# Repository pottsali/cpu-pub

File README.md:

# MUPS/16 Homebrew CPU project

This is public repo for files from the MUPS/16 homebrew CPU project. Please see http://mups16.net for details.

## Files

### Schematics
Currently I've only uploaded the schematics for the PCBs here, and will add more as I complete the last few bits. Most of the schematics are documented on the MUPS/16 [website](http://mups16.net).

### Others
I have a few other sets of files to clean up and upload:
 - A gate-level simulation of the whole system in [Digital](https://github.com/hneemann/Digital) format
 - Microcode generation, for the control ROMs
 - An assembler
 - A very basic monitor to test the system
 
These are not yet in a fit state to upload, but I will add them as I clean them up.

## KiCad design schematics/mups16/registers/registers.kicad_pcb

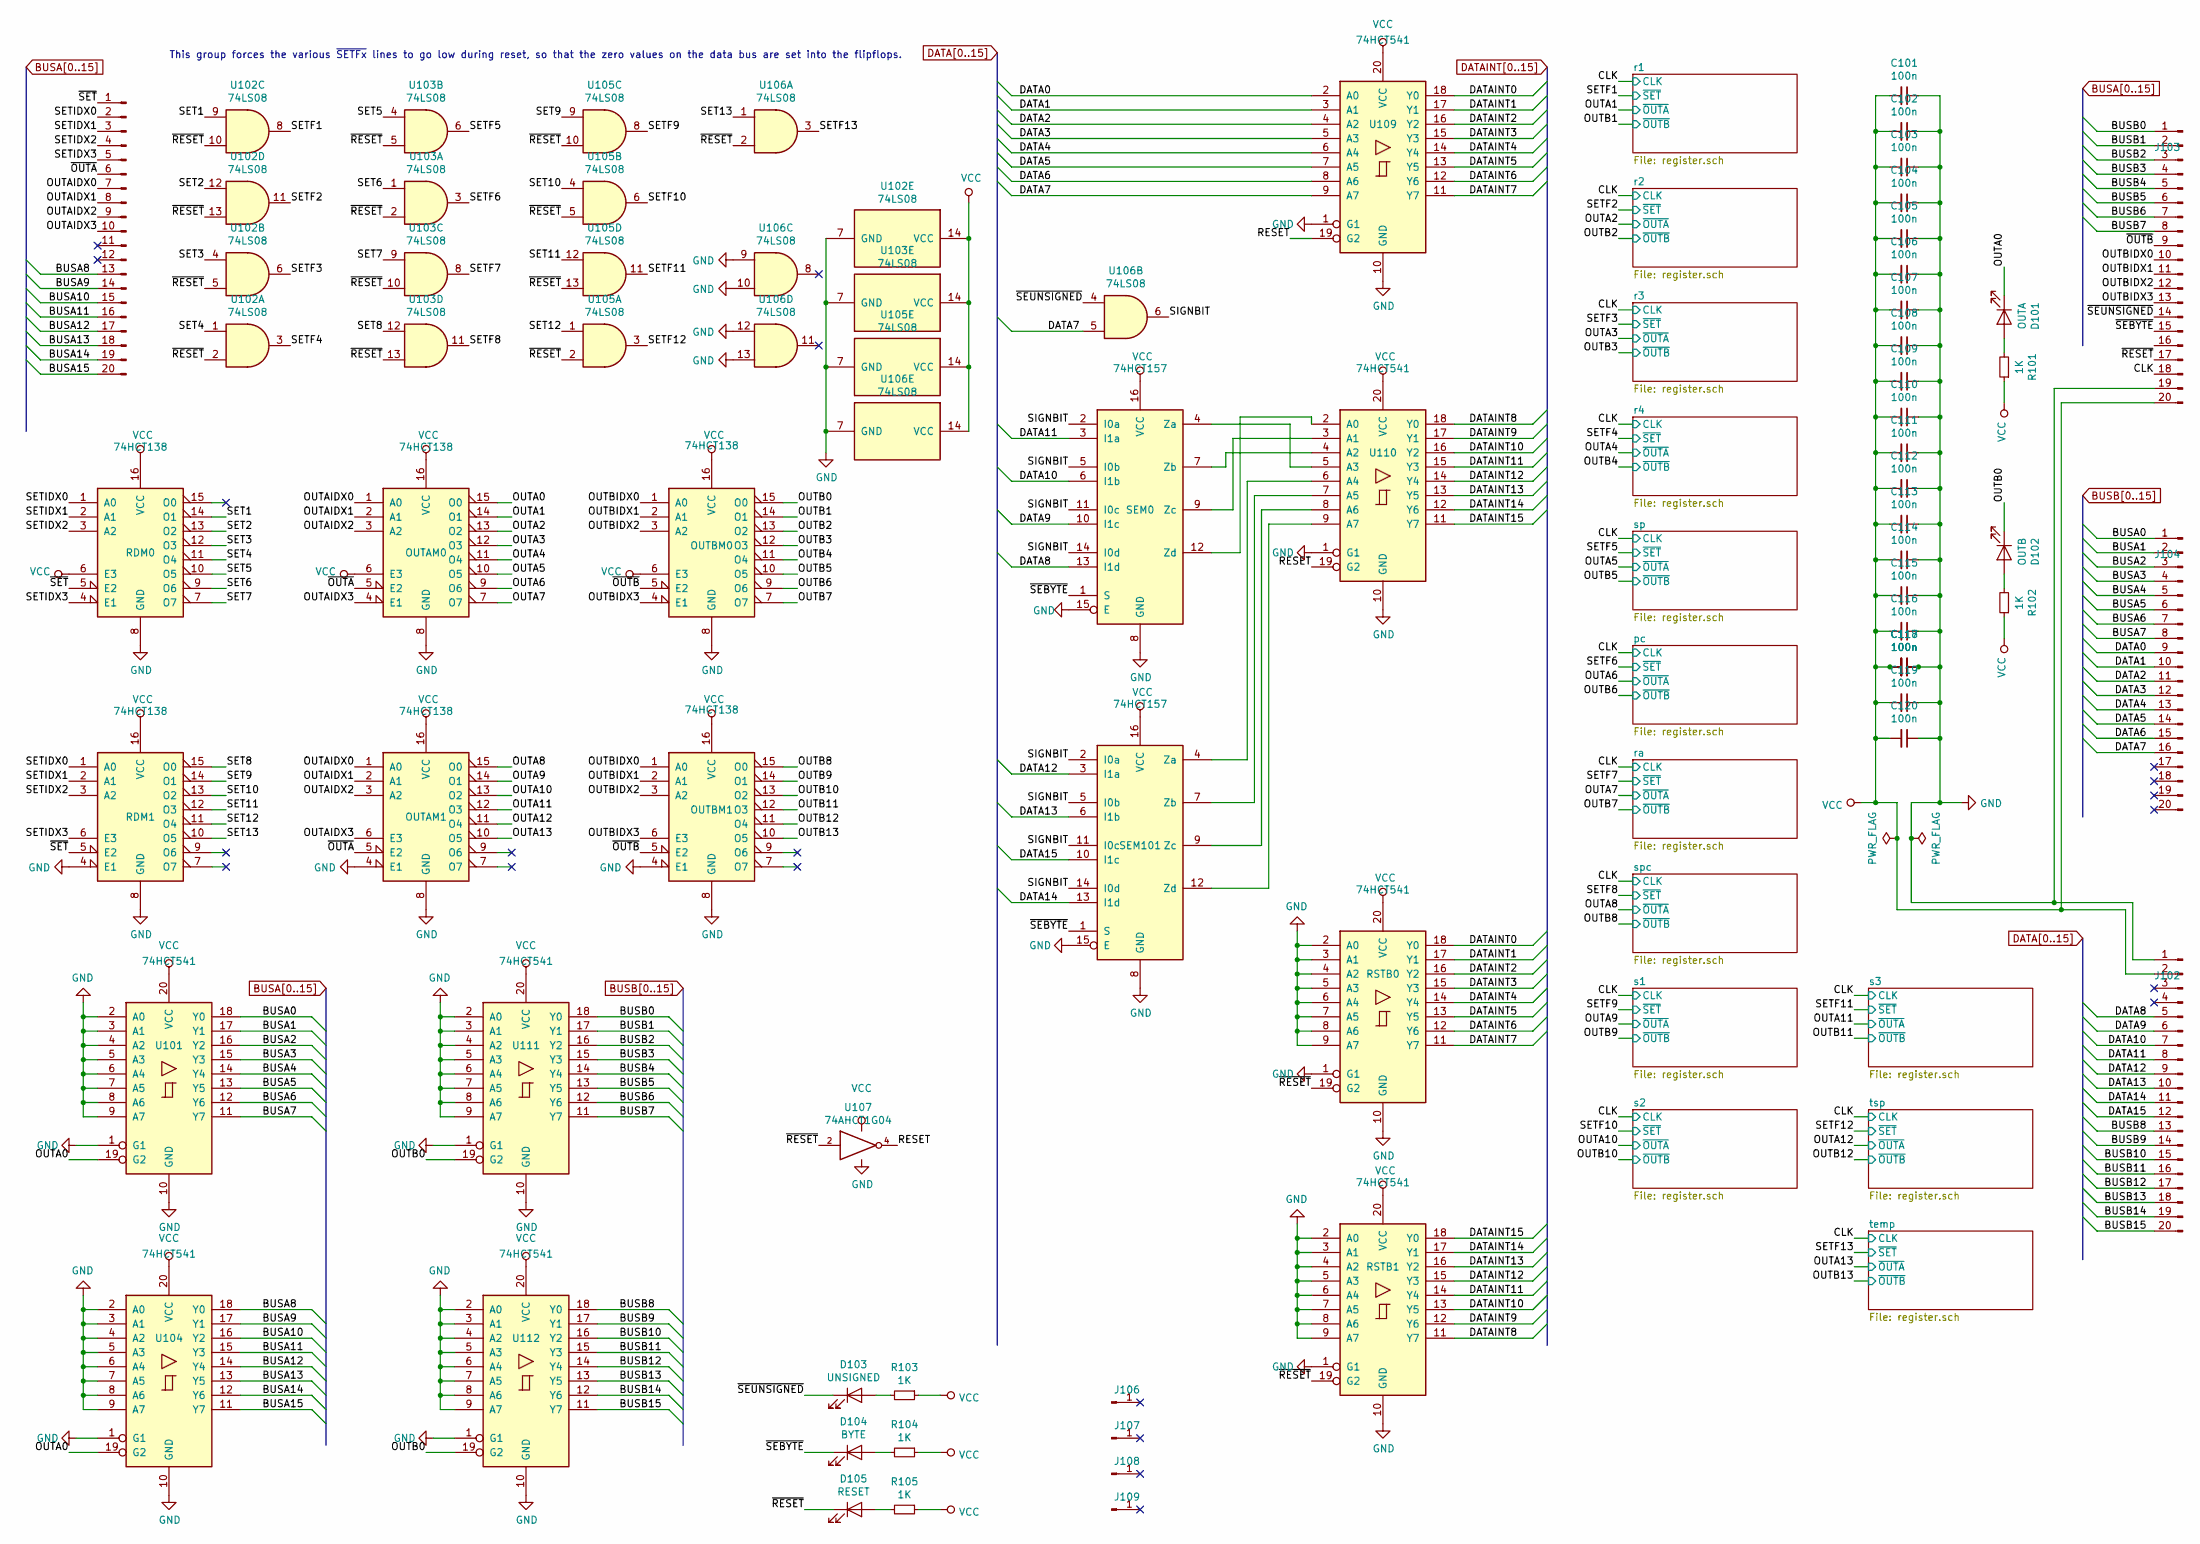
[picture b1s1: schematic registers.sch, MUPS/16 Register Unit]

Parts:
C101, C102, C103, C104, C105, C106, C107, C108, C109, C110, C111, C112, C113, C114, C115, C116, C117, C118, C119, C120: 100n; C_0805_2012Metric
D101: OUTA; LED_0805_2012Metric
D102: OUTB; LED_0805_2012Metric
D103: UNSIGNED; LED_0805_2012Metric
D104: BYTE; LED_0805_2012Metric
D105: RESET; LED_0805_2012Metric
J101: Conn_01x20_Male; PinHeader_1x20_P2.54mm_Vertical
J102, J103, J104: Conn_01x16_Male; PinHeader_1x20_P2.54mm_Vertical
J106, J107, J108, J109: Conn_01x01_Male; MountingHole_4mm_Pad
OUTAM0, OUTAM1: 74HCT138; SOIC-16_3.9x9.9mm_P1.27mm
OUTBM0, OUTBM1: 74HCT138; SOIC-16_3.9x9.9mm_P1.27mm
R101, R102, R103, R104, R105: 1K; R_0805_2012Metric
RDM0, RDM1: 74HCT138; SOIC-16_3.9x9.9mm_P1.27mm
RSTB0, RSTB1: 74HCT541; SOIC-20W_7.5x12.8mm_P1.27mm
SEM0, SEM101: 74HCT157; SOIC-16_3.9x9.9mm_P1.27mm
U101, U104, U109, U110, U111, U112: 74HCT541; SOIC-20W_7.5x12.8mm_P1.27mm
U102, U103, U105, U106: 74LS08; SOIC-14_3.9x8.7mm_P1.27mm
U107: 74AHCT1G04; TSOP-5_1.65x3.05mm_P0.95mm

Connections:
/CLK: J103.18; also elsewhere on the board
/OUTA0: D101.1 (K), OUTAM0.15 (O0), U101.19 (G2), U104.19 (G2)
/OUTA1: OUTAM0.14 (O1); also elsewhere on the board
/OUTA2: OUTAM0.13 (O2); also elsewhere on the board
/OUTA3: OUTAM0.12 (O3); also elsewhere on the board
/OUTA4: OUTAM0.11 (O4); also elsewhere on the board
/OUTA5: OUTAM0.10 (O5); also elsewhere on the board
/OUTA6: OUTAM0.9 (O6); also elsewhere on the board
/OUTA7: OUTAM0.7 (O7); also elsewhere on the board
/OUTA8: OUTAM1.15 (O0); also elsewhere on the board
/OUTA9: OUTAM1.14 (O1); also elsewhere on the board
/OUTA10: OUTAM1.13 (O2); also elsewhere on the board
/OUTA11: OUTAM1.12 (O3); also elsewhere on the board
/OUTA12: OUTAM1.11 (O4); also elsewhere on the board
/OUTA13: OUTAM1.10 (O5); also elsewhere on the board
/OUTAIDX0: J101.7, OUTAM0.1 (A0), OUTAM1.1 (A0)
/OUTAIDX1: J101.8, OUTAM0.2 (A1), OUTAM1.2 (A1)
/OUTAIDX2: J101.9, OUTAM0.3 (A2), OUTAM1.3 (A2)
/OUTAIDX3: J101.10, OUTAM0.4 (E1), OUTAM1.6 (E3)
/OUTB0: D102.1 (K), OUTBM0.15 (O0), U111.19 (G2), U112.19 (G2)
/OUTB1: OUTBM0.14 (O1); also elsewhere on the board
/OUTB2: OUTBM0.13 (O2); also elsewhere on the board
/OUTB3: OUTBM0.12 (O3); also elsewhere on the board
/OUTB4: OUTBM0.11 (O4); also elsewhere on the board
/OUTB5: OUTBM0.10 (O5); also elsewhere on the board
/OUTB6: OUTBM0.9 (O6); also elsewhere on the board
/OUTB7: OUTBM0.7 (O7); also elsewhere on the board
/OUTB8: OUTBM1.15 (O0); also elsewhere on the board
/OUTB9: OUTBM1.14 (O1); also elsewhere on the board
/OUTB10: OUTBM1.13 (O2); also elsewhere on the board
/OUTB11: OUTBM1.12 (O3); also elsewhere on the board
/OUTB12: OUTBM1.11 (O4); also elsewhere on the board
/OUTB13: OUTBM1.10 (O5); also elsewhere on the board
/OUTBIDX0: J103.10, OUTBM0.1 (A0), OUTBM1.1 (A0)
/OUTBIDX1: J103.11, OUTBM0.2 (A1), OUTBM1.2 (A1)
/OUTBIDX2: J103.12, OUTBM0.3 (A2), OUTBM1.3 (A2)
/OUTBIDX3: J103.13, OUTBM0.4 (E1), OUTBM1.6 (E3)
/RESET: U107.4, U109.19 (G2), U110.19 (G2)
/SET1: RDM0.14 (O1), U102.9
/SET2: RDM0.13 (O2), U102.12
/SET3: RDM0.12 (O3), U102.4
/SET4: RDM0.11 (O4), U102.1
/SET5: RDM0.10 (O5), U103.4
/SET6: RDM0.9 (O6), U103.1
/SET7: RDM0.7 (O7), U103.9
/SET8: RDM1.15 (O0), U103.12
/SET9: RDM1.14 (O1), U105.9
/SET10: RDM1.13 (O2), U105.4
/SET11: RDM1.12 (O3), U105.12
/SET12: RDM1.11 (O4), U105.1
/SET13: RDM1.10 (O5), U106.1
/SETF1: U102.8; also elsewhere on the board
/SETF2: U102.11; also elsewhere on the board
/SETF3: U102.6; also elsewhere on the board
/SETF4: U102.3; also elsewhere on the board
/SETF5: U103.6; also elsewhere on the board
/SETF6: U103.3; also elsewhere on the board
/SETF7: U103.8; also elsewhere on the board
/SETF8: U103.11; also elsewhere on the board
/SETF9: U105.8; also elsewhere on the board
/SETF10: U105.6; also elsewhere on the board
/SETF11: U105.11; also elsewhere on the board
/SETF12: U105.3; also elsewhere on the board
/SETF13: U106.3; also elsewhere on the board
/SETIDX0: J101.2, RDM0.1 (A0), RDM1.1 (A0)
/SETIDX1: J101.3, RDM0.2 (A1), RDM1.2 (A1)
/SETIDX2: J101.4, RDM0.3 (A2), RDM1.3 (A2)
/SETIDX3: J101.5, RDM0.4 (E1), RDM1.6 (E3)
/SIGNBIT: SEM0.2 (I0a), SEM0.5 (I0b), SEM0.11 (I0c), SEM0.14 (I0d), SEM101.2 (I0a), SEM101.5 (I0b), SEM101.11 (I0c), SEM101.14 (I0d), U106.6
/~OUTA: J101.6, OUTAM0.5 (E2), OUTAM1.5 (E2)
/~OUTB: J103.9, OUTBM0.5 (E2), OUTBM1.5 (E2)
/~RESET: D105.1 (K), J103.17, RSTB0.19 (G2), RSTB1.19 (G2), U102.2, U102.5, U102.10, U102.13, U103.2, U103.5, U103.10, U103.13, U105.2, U105.5, U105.10, U105.13, U106.2, U107.2
/~SEBYTE: D104.1 (K), J103.15, SEM0.1 (S), SEM101.1 (S)
/~SET: J101.1, RDM0.5 (E2), RDM1.5 (E2)
/~SEUNSIGNED: D103.1 (K), J103.14, U106.4
BUSA0: J104.1, U101.18 (Y0); also elsewhere on the board
BUSA1: J104.2, U101.17 (Y1); also elsewhere on the board
BUSA2: J104.3, U101.16 (Y2); also elsewhere on the board
BUSA3: J104.4, U101.15 (Y3); also elsewhere on the board
BUSA4: J104.5, U101.14 (Y4); also elsewhere on the board
BUSA5: J104.6, U101.13 (Y5); also elsewhere on the board
BUSA6: J104.7, U101.12 (Y6); also elsewhere on the board
BUSA7: J104.8, U101.11 (Y7); also elsewhere on the board
BUSA8: J101.13, U104.18 (Y0); also elsewhere on the board
BUSA9: J101.14, U104.17 (Y1); also elsewhere on the board
BUSA10: J101.15, U104.16 (Y2); also elsewhere on the board
BUSA11: J101.16, U104.15 (Y3); also elsewhere on the board
BUSA12: J101.17, U104.14 (Y4); also elsewhere on the board
BUSA13: J101.18, U104.13 (Y5); also elsewhere on the board
BUSA14: J101.19, U104.12 (Y6); also elsewhere on the board
BUSA15: J101.20, U104.11 (Y7); also elsewhere on the board
BUSB0: J103.1, U111.18 (Y0); also elsewhere on the board
BUSB1: J103.2, U111.17 (Y1); also elsewhere on the board
BUSB2: J103.3, U111.16 (Y2); also elsewhere on the board
BUSB3: J103.4, U111.15 (Y3); also elsewhere on the board
BUSB4: J103.5, U111.14 (Y4); also elsewhere on the board
BUSB5: J103.6, U111.13 (Y5); also elsewhere on the board
BUSB6: J103.7, U111.12 (Y6); also elsewhere on the board
BUSB7: J103.8, U111.11 (Y7); also elsewhere on the board
BUSB8: J102.13, U112.18 (Y0); also elsewhere on the board
BUSB9: J102.14, U112.17 (Y1); also elsewhere on the board
BUSB10: J102.15, U112.16 (Y2); also elsewhere on the board
BUSB11: J102.16, U112.15 (Y3); also elsewhere on the board
BUSB12: J102.17, U112.14 (Y4); also elsewhere on the board
BUSB13: J102.18, U112.13 (Y5); also elsewhere on the board
BUSB14: J102.19, U112.12 (Y6); also elsewhere on the board
BUSB15: J102.20, U112.11 (Y7); also elsewhere on the board
DATA0: J104.9, U109.2 (A0)
DATA1: J104.10, U109.3 (A1)
DATA2: J104.11, U109.4 (A2)
DATA3: J104.12, U109.5 (A3)
DATA4: J104.13, U109.6 (A4)
DATA5: J104.14, U109.7 (A5)
DATA6: J104.15, U109.8 (A6)
DATA7: J104.16, U106.5, U109.9 (A7)
DATA8: J102.5, SEM0.13 (I1d)
DATA9: J102.6, SEM0.10 (I1c)
DATA10: J102.7, SEM0.6 (I1b)
DATA11: J102.8, SEM0.3 (I1a)
DATA12: J102.9, SEM101.3 (I1a)
DATA13: J102.10, SEM101.6 (I1b)
DATA14: J102.11, SEM101.13 (I1d)
DATA15: J102.12, SEM101.10 (I1c)
DATAINT0: RSTB0.18 (Y0), U109.18 (Y0); also elsewhere on the board
DATAINT1: RSTB0.17 (Y1), U109.17 (Y1); also elsewhere on the board
DATAINT2: RSTB0.16 (Y2), U109.16 (Y2); also elsewhere on the board
DATAINT3: RSTB0.15 (Y3), U109.15 (Y3); also elsewhere on the board
DATAINT4: RSTB0.14 (Y4), U109.14 (Y4); also elsewhere on the board
DATAINT5: RSTB0.13 (Y5), U109.13 (Y5); also elsewhere on the board
DATAINT6: RSTB0.12 (Y6), U109.12 (Y6); also elsewhere on the board
DATAINT7: RSTB0.11 (Y7), U109.11 (Y7); also elsewhere on the board
DATAINT8: RSTB1.11 (Y7), U110.18 (Y0); also elsewhere on the board
DATAINT9: RSTB1.12 (Y6), U110.17 (Y1); also elsewhere on the board
DATAINT10: RSTB1.13 (Y5), U110.16 (Y2); also elsewhere on the board
DATAINT11: RSTB1.14 (Y4), U110.15 (Y3); also elsewhere on the board
DATAINT12: RSTB1.15 (Y3), U110.14 (Y4); also elsewhere on the board
DATAINT13: RSTB1.16 (Y2), U110.13 (Y5); also elsewhere on the board
DATAINT14: RSTB1.17 (Y1), U110.12 (Y6); also elsewhere on the board
DATAINT15: RSTB1.18 (Y0), U110.11 (Y7); also elsewhere on the board
GND: C101.1, C102.1, C103.1, C104.1, C105.1, C106.1, C107.1, C108.1, C109.1, C110.1, C111.1, C112.1, C113.1, C114.1, C115.1, C116.1, C117.1, C118.1, C119.1, C120.1, J102.1, J103.19, OUTAM0.8 (GND), OUTAM1.4 (E1), OUTAM1.8 (GND), OUTBM0.8 (GND), OUTBM1.4 (E1), OUTBM1.8 (GND), RDM0.8 (GND), RDM1.4 (E1), RDM1.8 (GND), RSTB0.1 (G1), RSTB0.2 (A0), RSTB0.3 (A1), RSTB0.4 (A2), RSTB0.5 (A3), RSTB0.6 (A4), RSTB0.7 (A5), RSTB0.8 (A6), RSTB0.9 (A7), RSTB0.10 (GND), RSTB1.1 (G1), RSTB1.2 (A0), RSTB1.3 (A1), RSTB1.4 (A2), RSTB1.5 (A3), RSTB1.6 (A4), RSTB1.7 (A5), RSTB1.8 (A6), RSTB1.9 (A7), RSTB1.10 (GND), SEM0.8 (GND), SEM0.15 (E), SEM101.8 (GND), SEM101.15 (E), U101.1 (G1), U101.2 (A0), U101.3 (A1), U101.4 (A2), U101.5 (A3), U101.6 (A4), U101.7 (A5), U101.8 (A6), U101.9 (A7), U101.10 (GND), U102.7 (GND), U103.7 (GND), U104.1 (G1), U104.2 (A0), U104.3 (A1), U104.4 (A2), U104.5 (A3), U104.6 (A4), U104.7 (A5), U104.8 (A6), U104.9 (A7), U104.10 (GND), U105.7 (GND), U106.7 (GND), U106.9, U106.10, U106.12, U106.13, U107.3 (GND), U109.1 (G1), U109.10 (GND), U110.1 (G1), U110.10 (GND), U111.1 (G1), U111.2 (A0), U111.3 (A1), U111.4 (A2), U111.5 (A3), U111.6 (A4), U111.7 (A5), U111.8 (A6), U111.9 (A7), U111.10 (GND), U112.1 (G1), U112.2 (A0), U112.3 (A1), U112.4 (A2), U112.5 (A3), U112.6 (A4), U112.7 (A5), U112.8 (A6), U112.9 (A7), U112.10 (GND); also elsewhere on the board
unnamed: D101.2 (A), R101.2
unnamed: D102.2 (A), R102.2
unnamed: D103.2 (A), R103.2
unnamed: D104.2 (A), R104.2
unnamed: D105.2 (A), R105.2
unnamed: SEM0.4 (Za), U110.5 (A3)
unnamed: SEM0.7 (Zb), U110.4 (A2)
unnamed: SEM0.9 (Zc), U110.3 (A1)
unnamed: SEM0.12 (Zd), U110.2 (A0)
unnamed: SEM101.4 (Za), U110.6 (A4)
unnamed: SEM101.7 (Zb), U110.7 (A5)
unnamed: SEM101.9 (Zc), U110.8 (A6)
unnamed: SEM101.12 (Zd), U110.9 (A7)
VCC: C101.2, C102.2, C103.2, C104.2, C105.2, C106.2, C107.2, C108.2, C109.2, C110.2, C111.2, C112.2, C113.2, C114.2, C115.2, C116.2, C117.2, C118.2, C119.2, C120.2, J102.2, J103.20, OUTAM0.6 (E3), OUTAM0.16 (VCC), OUTAM1.16 (VCC), OUTBM0.6 (E3), OUTBM0.16 (VCC), OUTBM1.16 (VCC), R101.1, R102.1, R103.1, R104.1, R105.1, RDM0.6 (E3), RDM0.16 (VCC), RDM1.16 (VCC), RSTB0.20 (VCC), RSTB1.20 (VCC), SEM0.16 (VCC), SEM101.16 (VCC), U101.20 (VCC), U102.14 (VCC), U103.14 (VCC), U104.20 (VCC), U105.14 (VCC), U106.14 (VCC), U107.5 (VCC), U109.20 (VCC), U110.20 (VCC), U111.20 (VCC), U112.20 (VCC); also elsewhere on the board

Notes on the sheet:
This group forces the various ~SETFx~ lines to go low during reset, so that the zero values on the data bus are set into the flipflops.
